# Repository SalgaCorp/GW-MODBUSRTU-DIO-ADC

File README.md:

GW MODBUS RTU ADC DIGITAL InOut: Open Source

Image of the GW or Node with ESP32 from LILYGO.

View design attachments:

Information document in Spanish

[DOCUMENTO_INFORMATIVO_GATEWAY_MODBUS_v1_06122023.pdf](https://github.com/SalgaCorp/GW-MODBUSRTU-DIO-ADC/files/14130991/DOCUMENTO_INFORMATIVO_GATEWAY_MODBUS_v1_06122023.pdf)

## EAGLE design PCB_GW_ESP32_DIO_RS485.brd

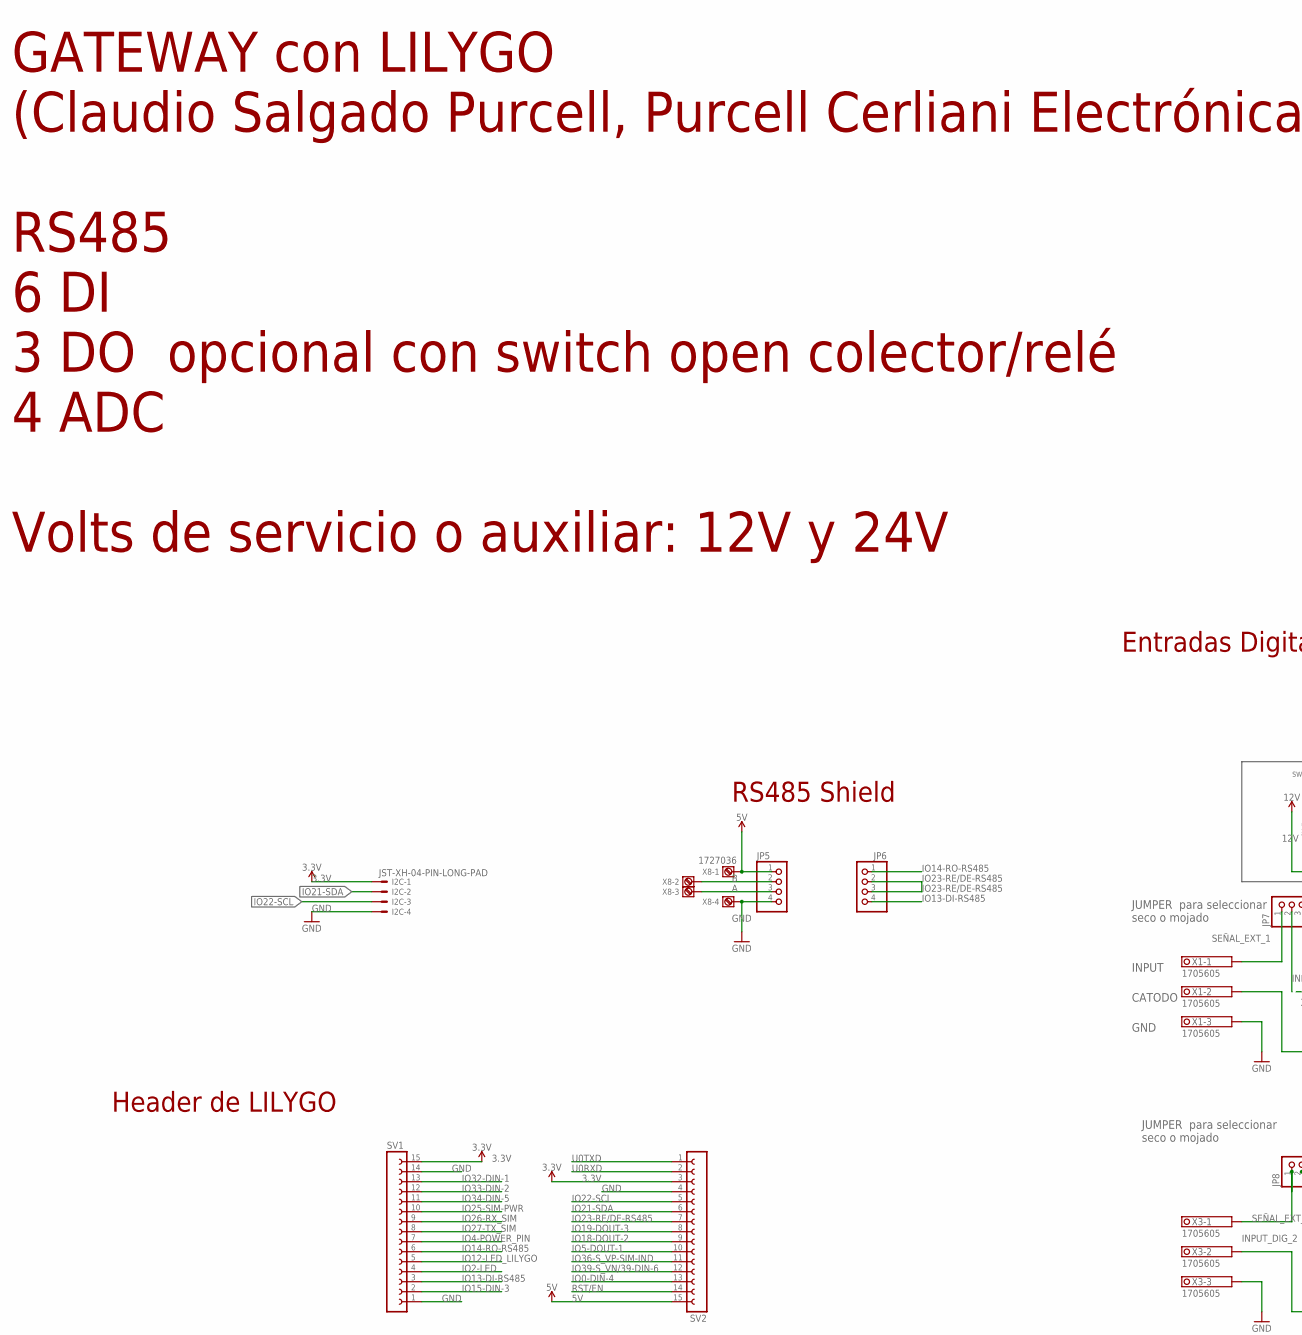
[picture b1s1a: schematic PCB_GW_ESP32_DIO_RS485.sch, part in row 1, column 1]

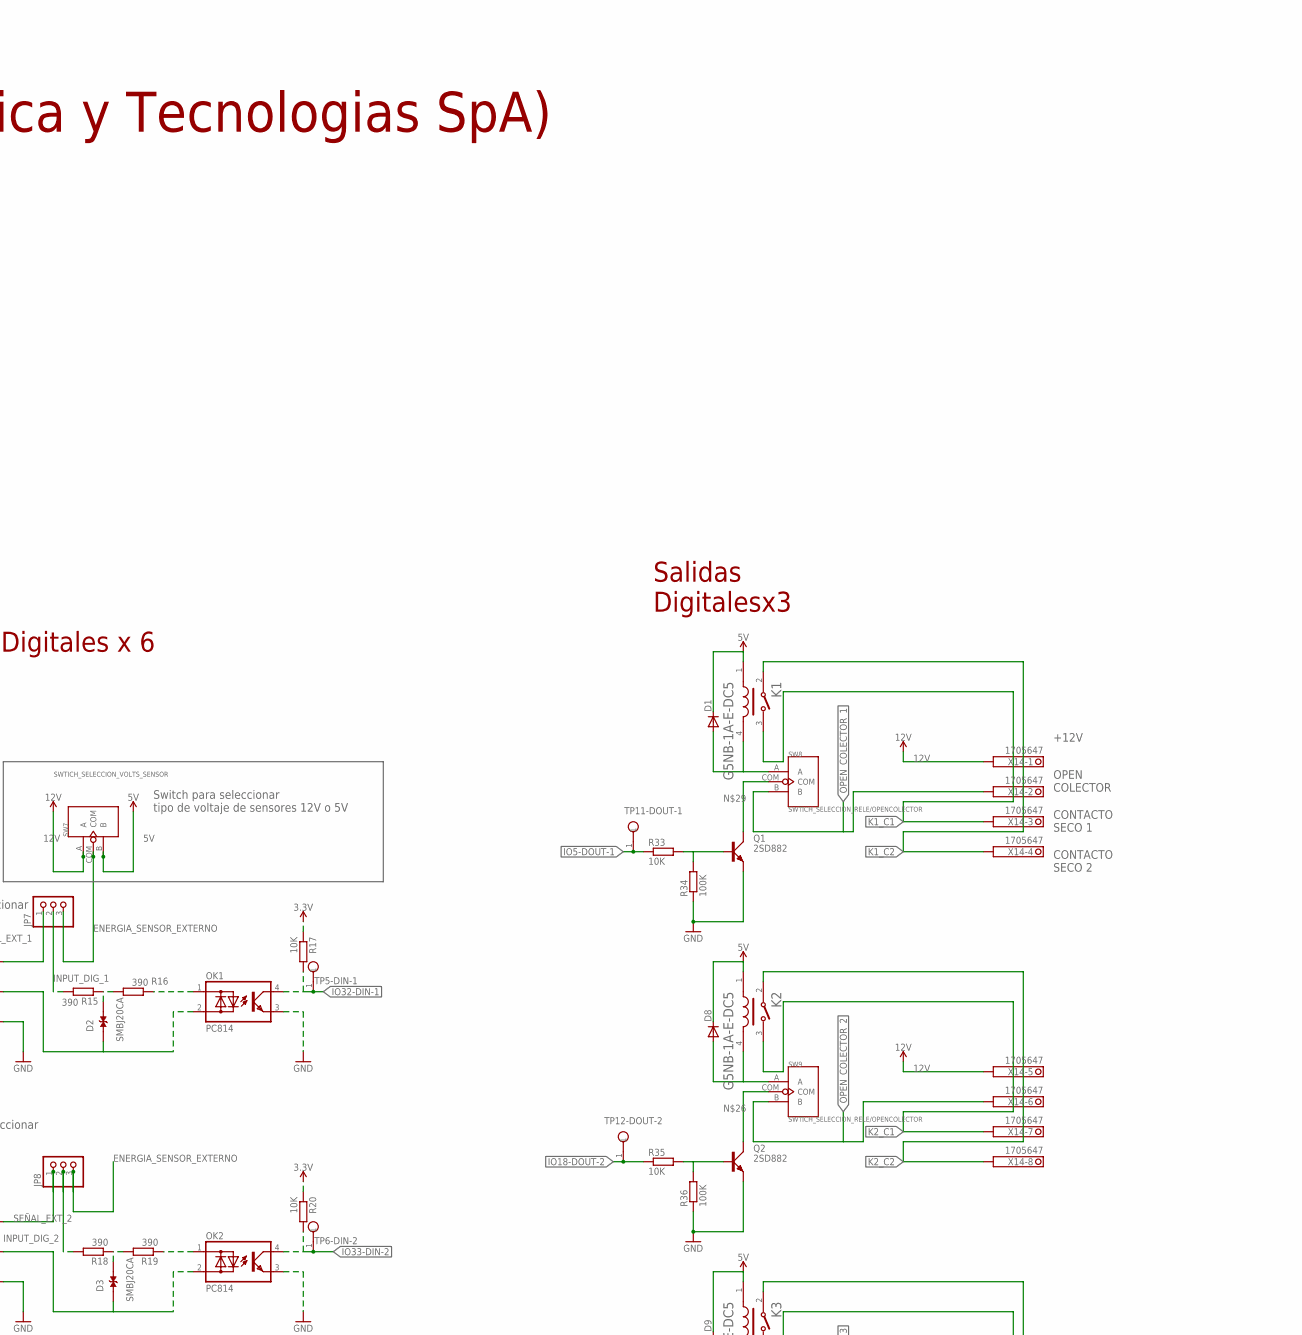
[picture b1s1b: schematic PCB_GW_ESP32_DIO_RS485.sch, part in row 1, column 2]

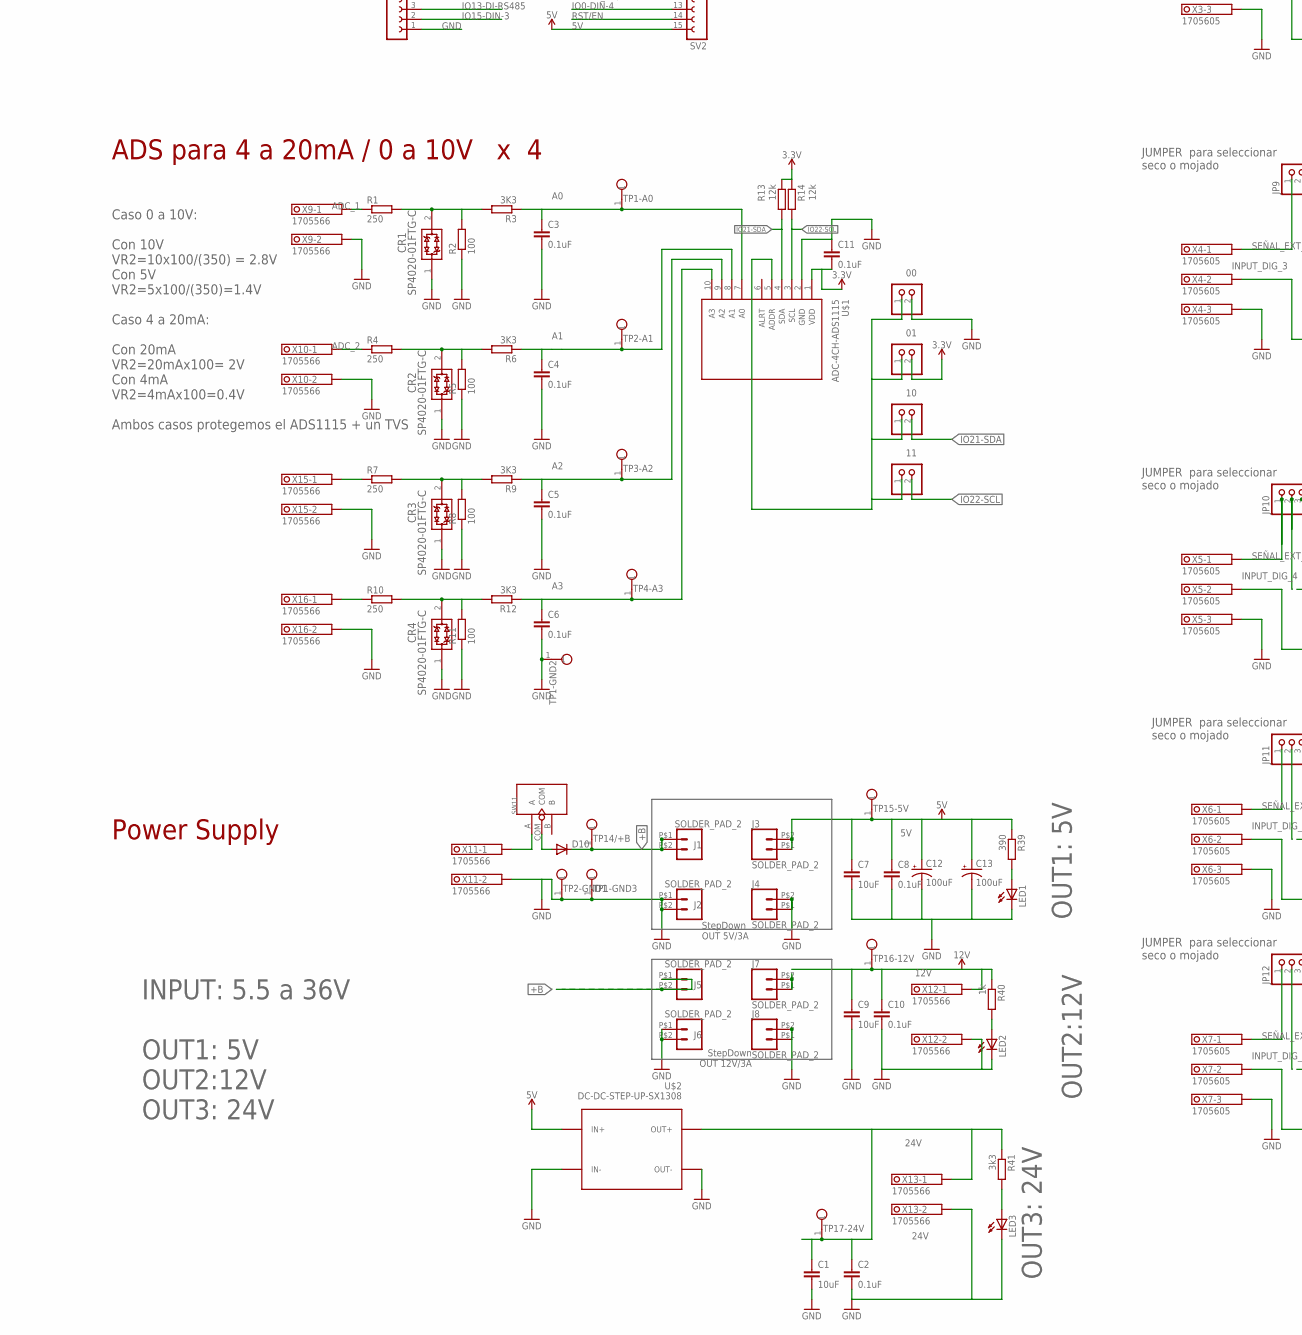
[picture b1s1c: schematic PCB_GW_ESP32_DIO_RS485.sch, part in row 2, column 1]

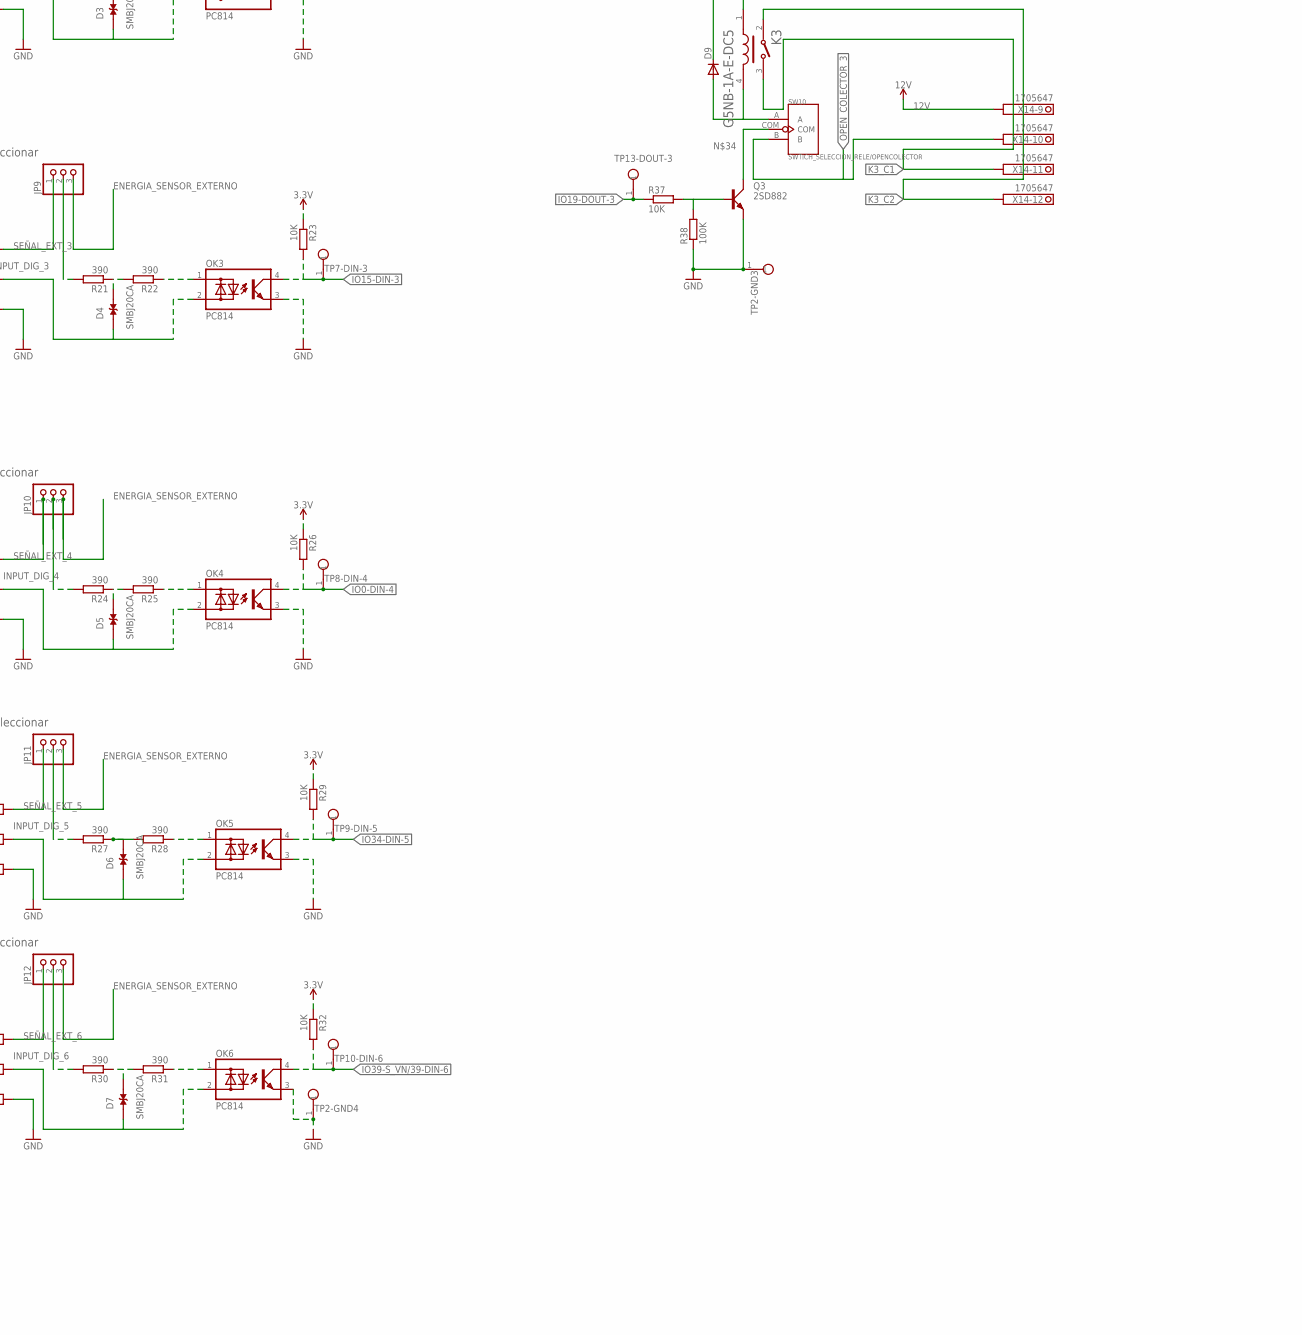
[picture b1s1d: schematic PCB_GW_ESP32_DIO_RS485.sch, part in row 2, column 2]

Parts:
C1, C7, C9: 10uF; 1206
C2, C3, C4, C5, C6, C8, C10, C11: 0.1uF; 1206
C12: 100uF; CPOL-RADIAL-2.5MM-6.5MM
C13: 100uF; PANASONIC_D
CR1, CR2, CR3, CR4: SP4020-01FTG-C; SOD323_LTF
D1, D8, D9, D10: DIODE-DO214AC; DO214AC
D2, D3, D4, D5, D6, D7: SMBJ20CA; DIOM4336X265N
I2C: JST-XH-04-PIN-LONG-PAD; JST-XH-04-PACKAGE-LONG-PAD
J1, J2, J3, J4, J5, J6, J7, J8: SOLDER_PAD_2
JP1: 00; 1X02
JP2: 01; 1X02
JP3: 10; 1X02
JP4: 11; 1X02
JP5, JP6: PINHD-1X4; 1X04
JP7, JP8, JP9, JP10, JP11, JP12: PINHD-1X3; 1X03
K1, K2, K3: OMRON_G5NB-1A-E-DC5OMRON_G5NB-1A-E-DC5_0_0; OMRON_G5NB-1A-E-DC5_0
LED1, LED2, LED3: LEDCHIPLED_1206; CHIPLED_1206
OK1, OK2, OK3, OK4, OK5, OK6: PC814; DIL04
Q1, Q2, Q3: 2SD882; TO126AV
R1, R4, R7, R10: 250; R1206
R2, R5, R8, R11: 100; R1206
R3, R6, R9, R12: 3K3; R1206
R13, R14: 12k; R1206
R15, R16, R18, R19, R21, R22, R24, R25, R27, R28, R30, R31, R39: 390; R1206
R17, R20, R23, R26, R29, R32, R33, R35, R37: 10K; R1206
R34, R36, R38: 100K; R1206
R40: 1k; R1206
R41: 3k3; R1206
SV1, SV2: FE15-1; FE15
SW7: SWTICH_SELECCION_VOLTS_SENSOR; SW5-2.0-8.8X4.4X4.7MM-90D
SW8, SW9, SW10: SWTICH_SELECCION_RELE/OPENCOLECTOR; SW5-2.0-8.8X4.4X4.7MM-90D
SW11: DIP-TOGGLE-SWITCH-ON-ON(3+2P-8.8X4.6MM)-90D; SW5-2.0-8.8X4.4X4.7MM-90D
TP1-A0, TP1-GND2, TP1-GND3, TP2-A1, TP2-GND1, TP2-GND3, TP2-GND4, TP3-A2, TP4-A3, TP5-DIN-1, TP6-DIN-2, TP7-DIN-3, TP8-DIN-4, TP9-DIN-5, TP10-DIN-6, TP11-DOUT-1, TP12-DOUT-2, TP13-DOUT-3, TP14/+B, TP15-5V, TP16-12V, TP17-24V: TESTPOINT
U$1: ADC-4CH-ADS1115
U$2: DC-DC-STEP-UP-SX1308
X1, X3, X4, X5, X6, X7: 1705605
X8: 1727036
X9, X10, X11, X12, X13, X15, X16: 1705566
X14: 1705647

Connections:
3.3V: C11.2, I2C.1, JP2.2, R13.1, R14.1, R17.1, R20.1, R23.1, R26.1, R29.1, R32.1, SV1.15, SV2.3, U$1.1 (VDD)
5V: C7.1, C8.1, C12.1 (+), C13.+, D1.C, D8.C, D9.C, J3.P$1 (1), J3.P$2 (2), JP5.1, K1.1, K2.1, K3.1, R39.1, SV2.15, SW7.B, TP15-5V.1, U$2.IN+, X8.1
12V: C9.1, C10.1, J7.P$1 (1), J7.P$2 (2), R40.1, SW7.A, TP16-12V.1, X12.1.1, X12.1.2, X14.1.1, X14.1.2, X14.5.1, X14.5.2, X14.9.1, X14.9.2
24V: C1.1, C2.1, R41.1, TP17-24V.1, U$2.OUT+, X13.1.1, X13.1.2
+B: D10.C, J1.P$1 (1), J1.P$2 (2), J5.P$1 (1), J5.P$2 (2), TP14/+B.1
A: JP5.3, X8.3
A0: C3.1, R3.1, TP1-A0.1, U$1.7 (A0)
A1: C4.1, R6.1, TP2-A1.1, U$1.8 (A1)
A2: C5.1, R9.1, TP3-A2.1, U$1.9 (A2)
A3: C6.1, R12.1, TP4-A3.1, U$1.10 (A3)
ADC_1: R1.1, X9.1.1, X9.1.2
ADC_2: R4.1, X10.1.1, X10.1.2
ADC_3: R7.1, X15.1.1, X15.1.2
ADC_4: R10.1, X16.1.1, X16.1.2
B: JP5.2, X8.2
ENERGIA_SENSOR_EXTERNO: JP7.3, JP8.3, JP9.3, JP10.3, JP11.3, JP12.3, SW7.COM
GND: C1.2, C2.2, C3.2, C4.2, C5.2, C6.2, C7.2, C8.2, C9.2, C10.2, C11.1, C12.2 (-), C13.-, CR1.1, CR2.1, CR3.1, CR4.1, I2C.4, J2.P$1 (1), J2.P$2 (2), J4.P$1 (1), J4.P$2 (2), J6.P$1 (1), J6.P$2 (2), J8.P$1 (1), J8.P$2 (2), JP1.2, JP5.4, LED1.C, LED2.C, LED3.C, OK1.3 (E), OK2.3 (E), OK3.3 (E), OK4.3 (E), OK5.3 (E), OK6.3 (E), Q1.E, Q2.E, Q3.E, R2.1, R5.1, R8.1, R11.1, R34.1, R36.1, R38.1, SV1.1, SV1.14, SV2.4, TP1-GND2.1, TP1-GND3.1, TP2-GND1.1, TP2-GND3.1, TP2-GND4.1, U$1.2 (GND), U$2.IN-, U$2.OUT-, X1.3.1, X1.3.2, X3.3.1, X3.3.2, X4.3.1, X4.3.2, X5.3.1, X5.3.2, X6.3.1, X6.3.2, X7.3.1, X7.3.2, X8.4, X9.2.1, X9.2.2, X10.2.1, X10.2.2, X11.2.1, X11.2.2, X12.2.1, X12.2.2, X13.2.1, X13.2.2, X15.2.1, X15.2.2, X16.2.1, X16.2.2
INPUT_DIG_1: JP7.2, R15.2
INPUT_DIG_2: JP8.2, R18.2
INPUT_DIG_3: JP9.2, R21.2
INPUT_DIG_4: JP10.2, R24.2
INPUT_DIG_5: JP11.2, R27.2
INPUT_DIG_6: JP12.2, R30.2
IO0-DIN-4: OK4.4 (C), R26.2, SV2.13, TP8-DIN-4.1
IO2-LED: SV1.4
IO4-POWER_PIN: SV1.7
IO5-DOUT-1: R33.1, SV2.10, TP11-DOUT-1.1
IO12-LED_LILYGO: SV1.5
IO13-DI-RS485: JP6.4, SV1.3
IO14-RO-RS485: JP6.1, SV1.6
IO15-DIN-3: OK3.4 (C), R23.2, SV1.2, TP7-DIN-3.1
IO18-DOUT-2: R35.1, SV2.9, TP12-DOUT-2.1
IO19-DOUT-3: R37.1, SV2.8, TP13-DOUT-3.1
IO21-SDA: I2C.2, JP3.2, R13.2, SV2.6, U$1.4 (SDA)
IO22-SCL: I2C.3, JP4.2, R14.2, SV2.5, U$1.3 (SCL)
IO23-RE/DE-RS485: JP6.2, JP6.3, SV2.7
IO25-SIM-PWR: SV1.10
IO26-RX_SIM: SV1.9
IO27-TX_SIM: SV1.8
IO32-DIN-1: OK1.4 (C), R17.2, SV1.13, TP5-DIN-1.1
IO33-DIN-2: OK2.4 (C), R20.2, SV1.12, TP6-DIN-2.1
IO34-DIN-5: OK5.4 (C), R29.2, SV1.11, TP9-DIN-5.1
IO36-S_VP-SIM-IND: SV2.11
IO39-S_VN/39-DIN-6: OK6.4 (C), R32.2, SV2.12, TP10-DIN-6.1
K1_C1: K1.3, X14.3.1, X14.3.2
K1_C2: K1.2, X14.4.1, X14.4.2
K2_C1: K2.3, X14.7.1, X14.7.2
K2_C2: K2.2, X14.8.1, X14.8.2
K3_C1: K3.3, X14.11.1, X14.11.2
K3_C2: K3.2, X14.12.1, X14.12.2
unnamed: LED1.A, R39.2
unnamed: CR2.2, R4.2, R5.2, R6.2
unnamed: CR1.2, R1.2, R2.2, R3.2
unnamed: CR3.2, R7.2, R8.2, R9.2
unnamed: CR4.2, R10.2, R11.2, R12.2
unnamed: JP1.1, JP2.1, JP3.1, JP4.1, U$1.5 (ADDR)
unnamed: OK1.1 (AC1), R16.1
unnamed: D2.2, R15.1, R16.2
unnamed: OK2.1 (AC1), R19.1
unnamed: D3.2, R18.1, R19.2
unnamed: OK3.1 (AC1), R22.1
unnamed: D4.2, R21.1, R22.2
unnamed: OK4.1 (AC1), R25.1
unnamed: D5.2, R24.1, R25.2
unnamed: Q1.B, R33.2, R34.2
unnamed: OK5.1 (AC1), R28.1
unnamed: D6.2, R27.1, R28.2
unnamed: Q2.B, R35.2, R36.2
unnamed: Q2.C, SW9.COM
unnamed: OK6.1 (AC1), R31.1
unnamed: D7.2, R30.1, R31.2
unnamed: Q1.C, SW8.COM
unnamed: D1.A, K1.4, SW8.A
unnamed: D8.A, K2.4, SW9.A
unnamed: D10.A, SW11.COM
unnamed: Q3.B, R37.2, R38.2
unnamed: Q3.C, SW10.COM
unnamed: D9.A, K3.4, SW10.A
unnamed: LED3.A, R41.2
unnamed: LED2.A, R40.2
OPEN_COLECTOR_1: SW8.B, X14.2.1, X14.2.2
OPEN_COLECTOR_2: SW9.B, X14.6.1, X14.6.2
OPEN_COLECTOR_3: SW10.B, X14.10.1, X14.10.2
POWER_IN: SW11.A, X11.1.1, X11.1.2
RST/EN: SV2.14
SEÑAL_EXT_1: JP7.1, X1.1.1, X1.1.2
SEÑAL_EXT_2: JP8.1, X3.1.1, X3.1.2
SEÑAL_EXT_3: JP9.1, X4.1.1, X4.1.2
SEÑAL_EXT_4: JP10.1, X5.1.1, X5.1.2
SEÑAL_EXT_5: JP11.1, X6.1.1, X6.1.2
SEÑAL_EXT_6: JP12.1, X7.1.1, X7.1.2
SPDT1: D2.1, OK1.2 (AC2), X1.2.1, X1.2.2
SPDT2: D3.1, OK2.2 (AC2), X3.2.1, X3.2.2
SPDT3: D4.1, OK3.2 (AC2), X4.2.1, X4.2.2
SPDT4: D5.1, OK4.2 (AC2), X5.2.1, X5.2.2
SPDT5: D6.1, OK5.2 (AC2), X6.2.1, X6.2.2
SPDT6: D7.1, OK6.2 (AC2), X7.2.1, X7.2.2
U0RXD: SV2.2
U0TXD: SV2.1

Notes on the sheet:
Caso 0 a 10V: Con 10V VR2=10x100/(350) = 2.8V Con 5V VR2=5x100/(350)=1.4V Caso 4 a 20mA: Con 20mA VR2=20mAx100= 2V Con 4mA VR2=4mAx100=0.4V Ambos casos protegemos el ADS1115 + un TVS
ADS para 4 a 20mA / 0 a 10V x 4
Header de LILYGO
Entradas Digitales x 6
Salidas Digitalesx3
RS485 Shield
Power Supply
INPUT: 5.5 a 36V OUT1: 5V OUT2:12V OUT3: 24V
StepDown OUT 5V/3A
StepDown OUT 12V/3A
Switch para seleccionar tipo de voltaje de sensores 12V o 5V
JUMPER para seleccionar seco o mojado
OUT1: 5V
OUT2:12V
OUT3: 24V
GATEWAY con LILYGO (Claudio Salgado Purcell, Purcell Cerliani Electrónica y Tecnologias SpA) RS485 6 DI 3 DO opcional con switch open colector/relé 4 ADC Volts de servicio o auxiliar: 12V y 24V
GND
CATODO
INPUT
CONTACTO SECO 2
CONTACTO SECO 1
OPEN COLECTOR
+12V

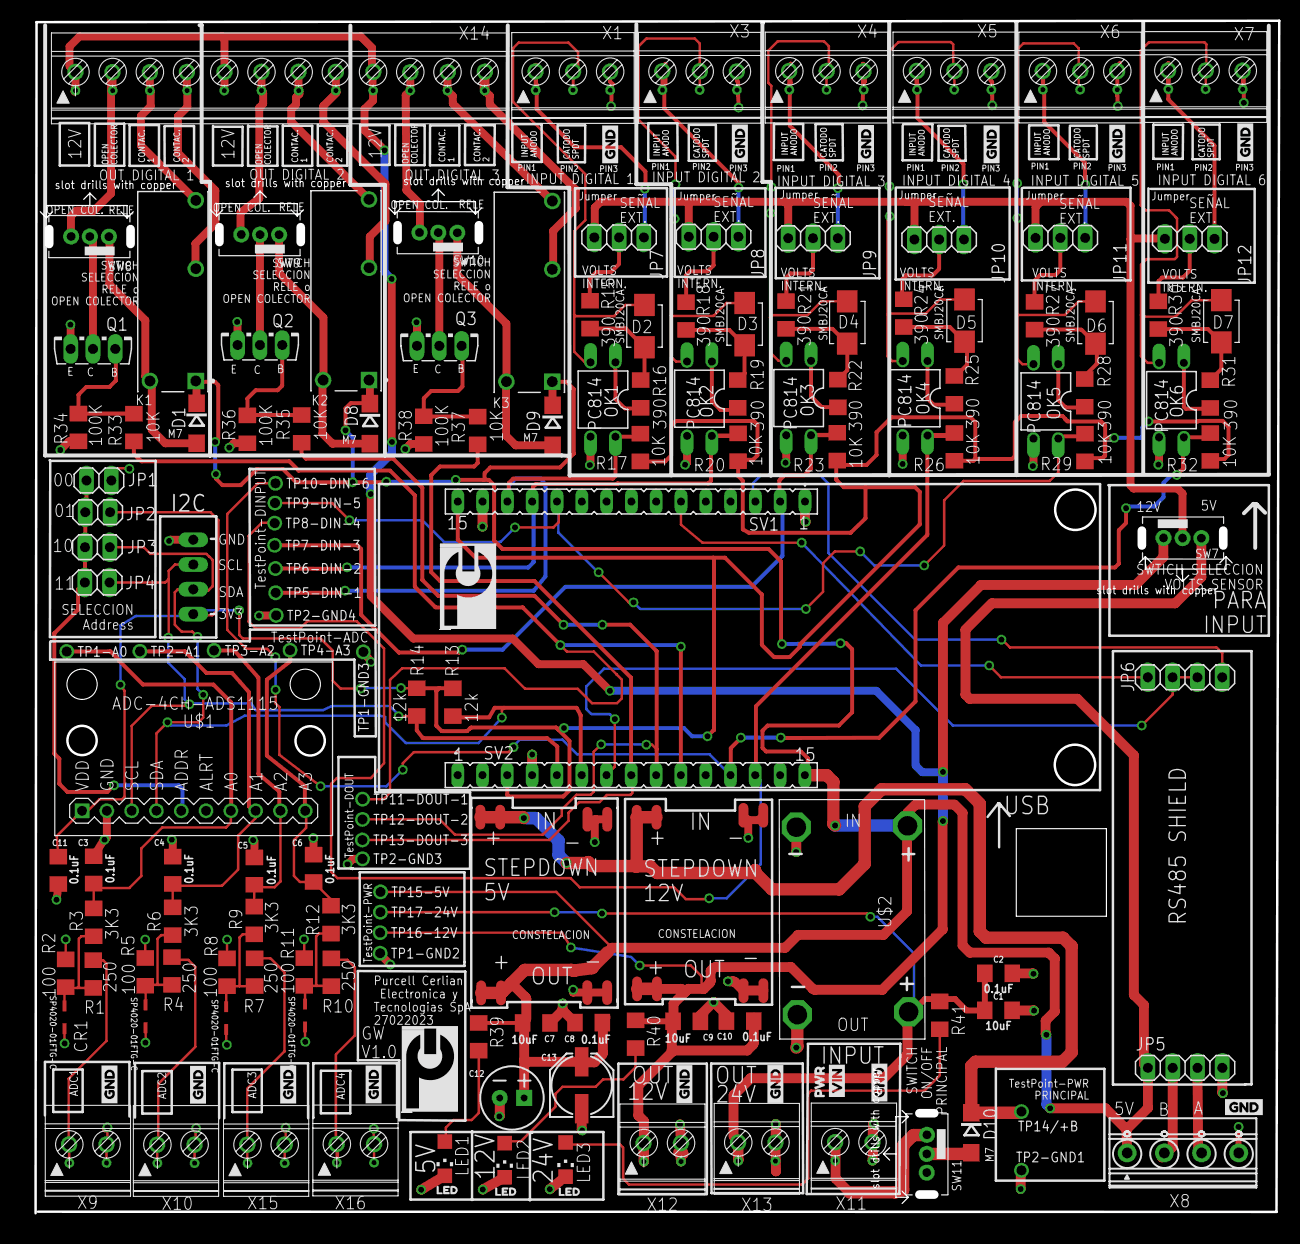
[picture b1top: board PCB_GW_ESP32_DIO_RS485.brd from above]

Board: 2 copper layers, 127.4 x 122.1 mm, 169 parts (0 on the bottom side), 89 nets.

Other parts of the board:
U$3: VIN_P
U$4: PWR_TO
U$5, U$6, U$7: LED_TO
U$8, U$9, U$10, U$11, U$12, U$13, U$14, U$15, U$16, U$17, U$18, U$19, U$20, U$21: GND_P

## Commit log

2024-02-01 FW TEST Validation
2024-02-01 PCB Design Files
2024-02-01 Update README.md
    Plus

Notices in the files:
parts and their libraries:
cargador microusb-modules lib: Released under the Creative Commons Attribution 4.0 International License: http://creativecommons.org/licenses/by/4.0
SparkFun-Capacitors: Licensing: Creative Commons ShareAlike 4.0 International - https://creativecommons.org/licenses/by-sa/4.0
